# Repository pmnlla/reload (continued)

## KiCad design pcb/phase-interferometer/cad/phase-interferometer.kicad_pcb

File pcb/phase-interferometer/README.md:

# Phase Interferometer
### Max Kendall

At a high level, this is a system that uses 3 antennas (elements) to esitmate the approximate direction of an incoming radio signal. This means that you're able to get the location of an object in a protocol-agnostic manner! The vision is that this is mostly portable (aside from the antennas) and can be whipped out anywhere to get a quick bearing.

The hardware contains 3 RF frontends, including 1 amplifier, 1 mixer, and 1 filter for each element. It uses a mixer to be able to directly feed the signal into the onboard RP2040 microcontroller. It then would perform a phase analysis to determine which signals reach the pins first.
Since we're dealing with a phased-array, we need to perform length tuning to make sure all the tracks are electrically the same length. KiCAD has a great built-in tool for this!

Here's the features/specs:
- RP2040 MCU
- 3x 433 MHz frontends
- USB-C
- 4-layer board
- via fencing/stitching
- broken-out gpio headers for all free pins
- LO for all mixers

## Super cool pics:

Main repository can be found [here](https://github.com/maxsrobotics/phase-interferometer).

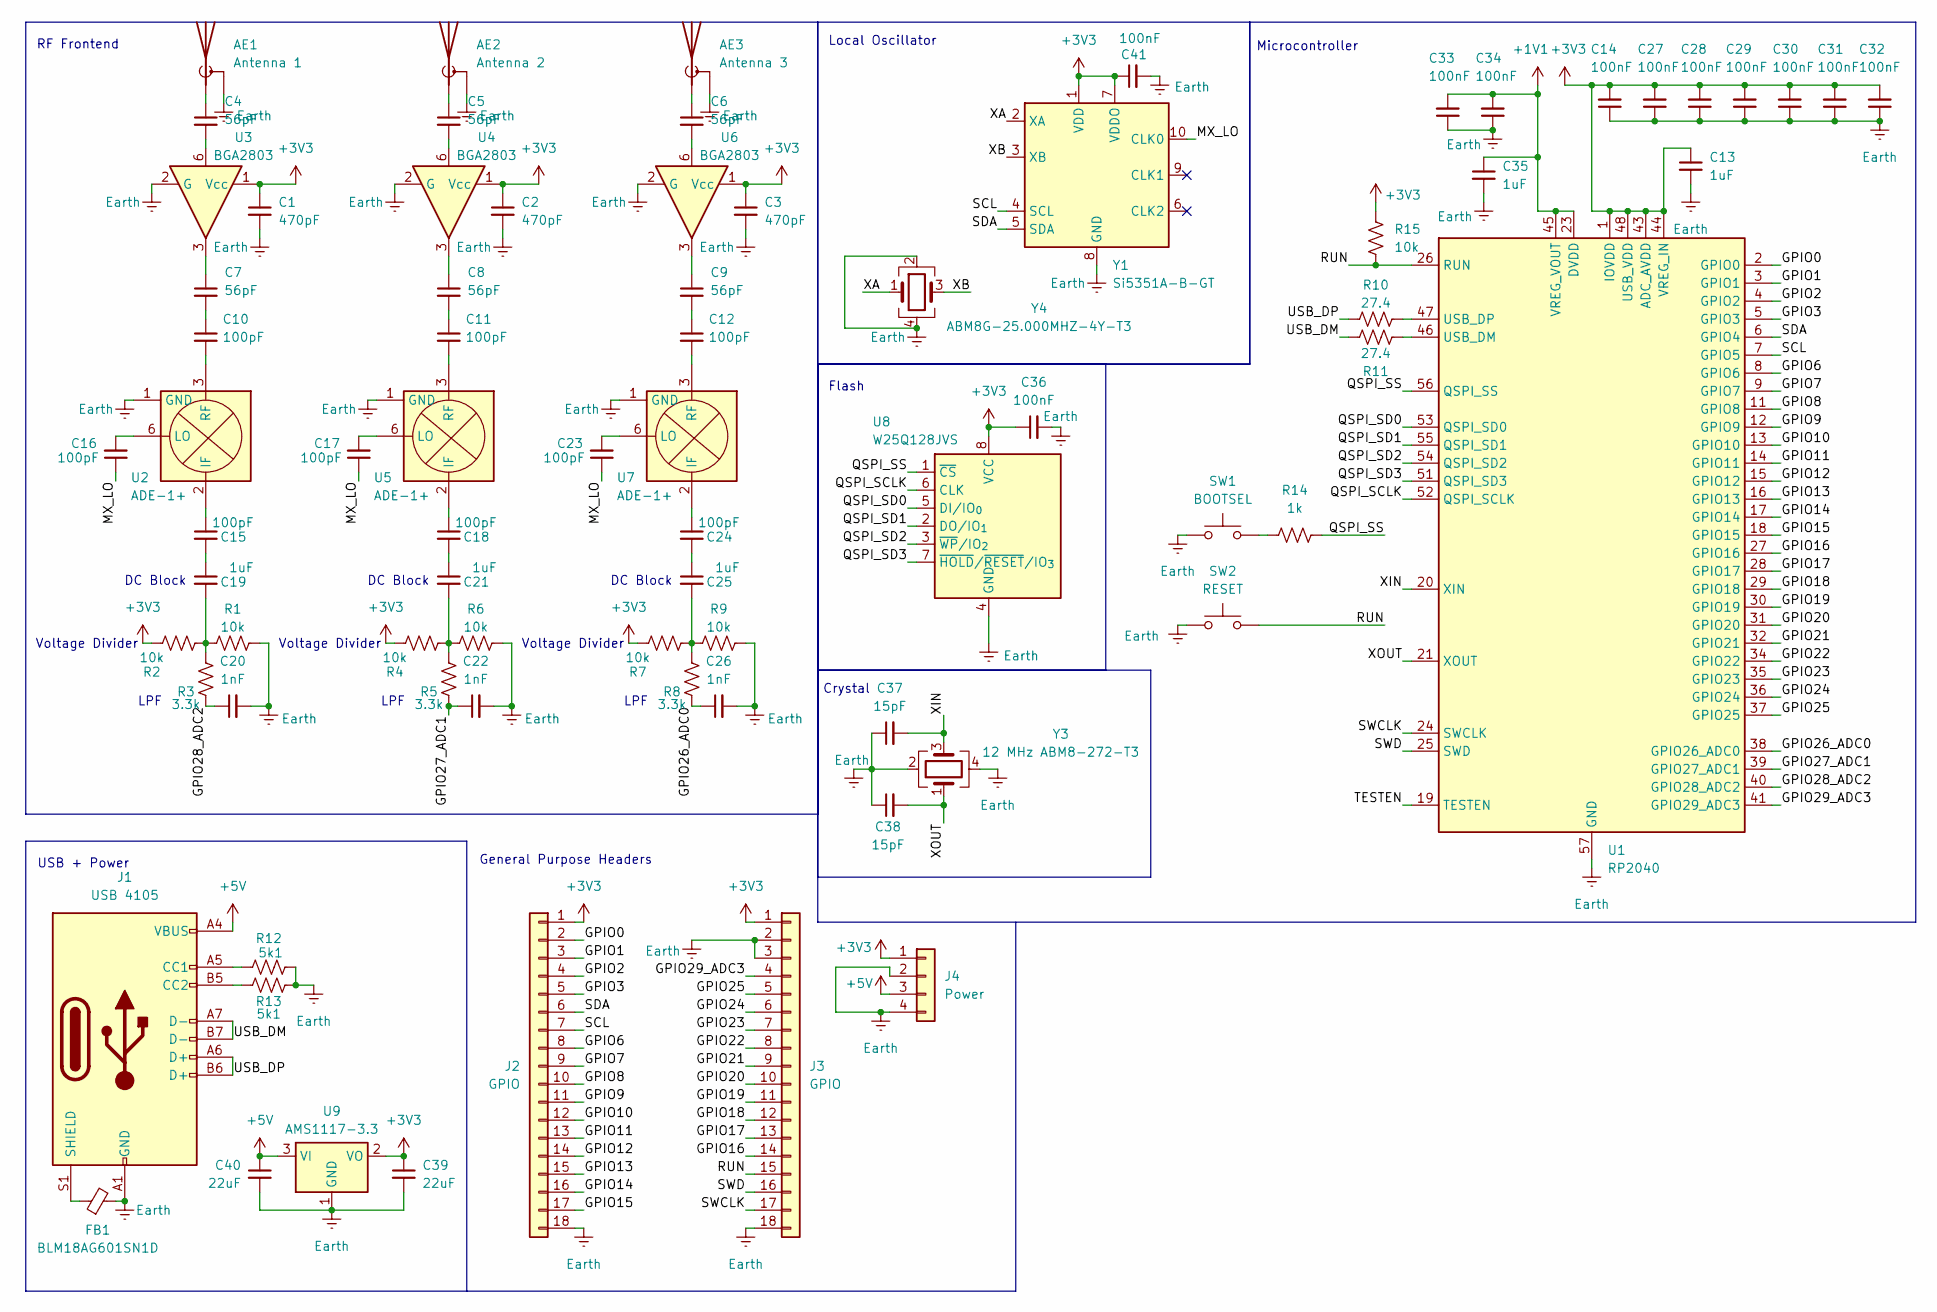
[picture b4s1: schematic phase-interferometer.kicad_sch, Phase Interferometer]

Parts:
AE1: Antenna 1; PinSocket_1x02_P2.54mm_Vertical
AE2: Antenna 2; PinSocket_1x02_P2.54mm_Vertical
AE3: Antenna 3; PinSocket_1x02_P2.54mm_Vertical
C1, C2, C3: 470pF; C_0603_1608Metric
C4, C5, C6, C7, C8, C9: 56pF; C_0603_1608Metric
C10, C11, C12, C15, C16, C17, C18, C23, C24: 100pF; C_0603_1608Metric
C13, C19, C21, C25, C35: 1uF; C_0603_1608Metric
C14, C27, C28, C29, C30, C31, C32, C33, C34, C36, C41: 100nF; C_0603_1608Metric
C20, C22, C26: 1nF; C_0603_1608Metric
C37, C38: 15pF; C_0603_1608Metric
C39, C40: 22uF; C_0603_1608Metric
FB1: BLM18AG601SN1D; R_0201_0603Metric
J1: USB 4105; USB_C_Receptacle_GCT_USB4105-xx-A_16P_TopMnt_Horizontal
J2, J3: GPIO; PinSocket_1x18_P2.54mm_Vertical
J4: Power; PinSocket_1x04_P2.54mm_Vertical
R1, R2, R4, R6, R7, R9, R15: 10k; R_0603_1608Metric
R3, R5, R8: 3.3k; R_0603_1608Metric
R10, R11: 27.4; R_0603_1608Metric
R12, R13: 5k1; R_0603_1608Metric
R14: 1k; R_0603_1608Metric
SW1: BOOTSEL; SW_Tactile_SPST_NO_Straight_CK_PTS636Sx25SMTRLFS
SW2: RESET; SW_Tactile_SPST_NO_Straight_CK_PTS636Sx25SMTRLFS
U1: RP2040; QFN-56-1EP_7x7mm_P0.4mm_EP3.2x3.2mm
U2, U5, U7: ADE-1+; Mini-Circuits_CD636_H4.11mm
U3, U4, U6: BGA2803; SOT-363_SC-70-6
U8: W25Q128JVS; SOIC-8_5.3x5.3mm_P1.27mm
U9: AMS1117-3.3; SOT-223-3_TabPin2
Y1: Si5351A-B-GT; MSOP-10_3x3mm_P0.5mm
Y3: 12 MHz ABM8-272-T3; Crystal_SMD_Abracon_ABM8G-4Pin_3.2x2.5mm
Y4: ABM8G-25.000MHZ-4Y-T3; Crystal_SMD_Abracon_ABM8G-4Pin_3.2x2.5mm

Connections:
+1V1: C33.2, C34.2, C35.1, U1.23 (DVDD), U1.45 (VREG_VOUT), U1.50 (DVDD)
+3V3: C1.1, C2.1, C3.1, C13.1, C14.2, C27.2, C28.2, C29.2, C30.2, C31.2, C32.2, C36.1, C39.1, C41.1, J2.1, J3.1, J4.1, R2.2, R4.2, R7.2, R15.1, U1.1 (IOVDD), U1.10 (IOVDD), U1.22 (IOVDD), U1.33 (IOVDD), U1.42 (IOVDD), U1.43 (ADC_AVDD), U1.44 (VREG_IN), U1.48 (USB_VDD), U1.49 (IOVDD), U3.1 (Vcc), U4.1 (Vcc), U6.1 (Vcc), U8.8 (VCC), U9.2 (VO), Y1.1 (VDD), Y1.7 (VDDO)
+5V: C40.1, J1.A4 (VBUS), J1.A9 (VBUS), J1.B4 (VBUS), J1.B9 (VBUS), J4.3, U9.3 (VI)
/GPIO0: J2.2, U1.2 (GPIO0)
/GPIO1: J2.3, U1.3 (GPIO1)
/GPIO2: J2.4, U1.4 (GPIO2)
/GPIO3: J2.5, U1.5 (GPIO3)
/GPIO6: J2.8, U1.8 (GPIO6)
/GPIO7: J2.9, U1.9 (GPIO7)
/GPIO8: J2.10, U1.11 (GPIO8)
/GPIO9: J2.11, U1.12 (GPIO9)
/GPIO10: J2.12, U1.13 (GPIO10)
/GPIO11: J2.13, U1.14 (GPIO11)
/GPIO12: J2.14, U1.15 (GPIO12)
/GPIO13: J2.15, U1.16 (GPIO13)
/GPIO14: J2.16, U1.17 (GPIO14)
/GPIO15: J2.17, U1.18 (GPIO15)
/GPIO16: J3.14, U1.27 (GPIO16)
/GPIO17: J3.13, U1.28 (GPIO17)
/GPIO18: J3.12, U1.29 (GPIO18)
/GPIO19: J3.11, U1.30 (GPIO19)
/GPIO20: J3.10, U1.31 (GPIO20)
/GPIO21: J3.9, U1.32 (GPIO21)
/GPIO22: J3.8, U1.34 (GPIO22)
/GPIO23: J3.7, U1.35 (GPIO23)
/GPIO24: J3.6, U1.36 (GPIO24)
/GPIO25: J3.5, U1.37 (GPIO25)
/GPIO26_ADC0: C26.1, R8.1, U1.38 (GPIO26_ADC0)
/GPIO27_ADC1: C22.1, R5.1, U1.39 (GPIO27_ADC1)
/GPIO28_ADC2: C20.1, R3.1, U1.40 (GPIO28_ADC2)
/GPIO29_ADC3: J3.4, U1.41 (GPIO29_ADC3)
/MX_LO: C16.1, C17.1, C23.1, Y1.10 (CLK0)
/QSPI_SCLK: U1.52 (QSPI_SCLK), U8.6 (CLK)
/QSPI_SD0: U1.53 (QSPI_SD0), U8.5 (DI/IO_{0})
/QSPI_SD1: U1.55 (QSPI_SD1), U8.2 (DO/IO_{1})
/QSPI_SD2: U1.54 (QSPI_SD2), U8.3 (~WP/IO_{2})
/QSPI_SD3: U1.51 (QSPI_SD3), U8.7 (~HOLD/~RESET/IO_{3})
/QSPI_SS: R14.2, U1.56 (QSPI_SS), U8.1 (~CS)
/RUN: J3.15, R15.2, SW2.2, U1.26 (RUN)
/SCL: J2.7, U1.7 (GPIO5), Y1.4 (SCL)
/SDA: J2.6, U1.6 (GPIO4), Y1.5 (SDA)
/SWCLK: J3.17, U1.24 (SWCLK)
/SWD: J3.16, U1.25 (SWD)
/TESTEN: U1.19 (TESTEN)
/USB_DM: J1.A7 (D-), J1.B7 (D-), R11.2
/USB_DP: J1.A6 (D+), J1.B6 (D+), R10.1
/XA: Y1.2 (XA), Y4.1
/XB: Y1.3 (XB), Y4.3
/XIN: C37.2, U1.20 (XIN), Y3.3
/XOUT: C38.2, U1.21 (XOUT), Y3.1
Earth: AE1.2 (Shield), AE2.2 (Shield), AE3.2 (Shield), C1.2, C2.2, C3.2, C13.2, C14.1, C20.2, C22.2, C26.2, C27.1, C28.1, C29.1, C30.1, C31.1, C32.1, C33.1, C34.1, C35.2, C36.2, C37.1, C38.1, C39.2, C40.2, C41.2, FB1.2, J1.A1 (GND), J1.A12 (GND), J1.B1 (GND), J1.B12 (GND), J2.18, J3.2, J3.3, J3.18, J4.2, J4.4, R1.2, R6.2, R9.2, R12.2, R13.2, SW1.1, SW2.1, U1.57 (GND), U2.1 (GND), U2.4 (GND), U2.5 (GND), U3.2 (G), U3.4 (G), U3.5 (G), U4.2 (G), U4.4 (G), U4.5 (G), U5.1 (GND), U5.4 (GND), U5.5 (GND), U6.2 (G), U6.4 (G), U6.5 (G), U7.1 (GND), U7.4 (GND), U7.5 (GND), U8.4 (GND), U9.1 (GND), Y1.8 (GND), Y3.2, Y3.4, Y4.2, Y4.4
unnamed: AE1.1 (A), C4.1
unnamed: AE2.1 (A), C5.1
unnamed: AE3.1 (A), C6.1
unnamed: C4.2, U3.6
unnamed: C5.2, U4.6
unnamed: C6.2, U6.6
unnamed: C7.1, U3.3
unnamed: C8.1, U4.3
unnamed: C9.1, U6.3
unnamed: C7.2, C10.1
unnamed: C8.2, C11.1
unnamed: C9.2, C12.1
unnamed: C15.2, C19.1
unnamed: C18.2, C21.1
unnamed: C19.2, R1.1, R2.1, R3.2
unnamed: C21.2, R4.1, R5.2, R6.1
unnamed: C24.2, C25.1
unnamed: C25.2, R7.1, R8.2, R9.1
unnamed: J1.A5 (CC1), R12.1
unnamed: J1.B5 (CC2), R13.1
unnamed: FB1.1, J1.S1 (SHIELD)
unnamed: R14.1, SW1.2
unnamed: R11.1, U1.46 (USB_DM)
unnamed: R10.2, U1.47 (USB_DP)
unnamed: C15.1, U2.2 (IF)
unnamed: C16.2, U2.6 (LO)
unnamed: C10.2, U2.3 (RF)
unnamed: C18.1, U5.2 (IF)
unnamed: C17.2, U5.6 (LO)
unnamed: C11.2, U5.3 (RF)
unnamed: C24.1, U7.2 (IF)
unnamed: C23.2, U7.6 (LO)
unnamed: C12.2, U7.3 (RF)

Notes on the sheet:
LPF
Local Oscillator
Voltage Divider
DC Block
USB + Power
General Purpose Headers
Microcontroller
Flash
Crystal
RF Frontend

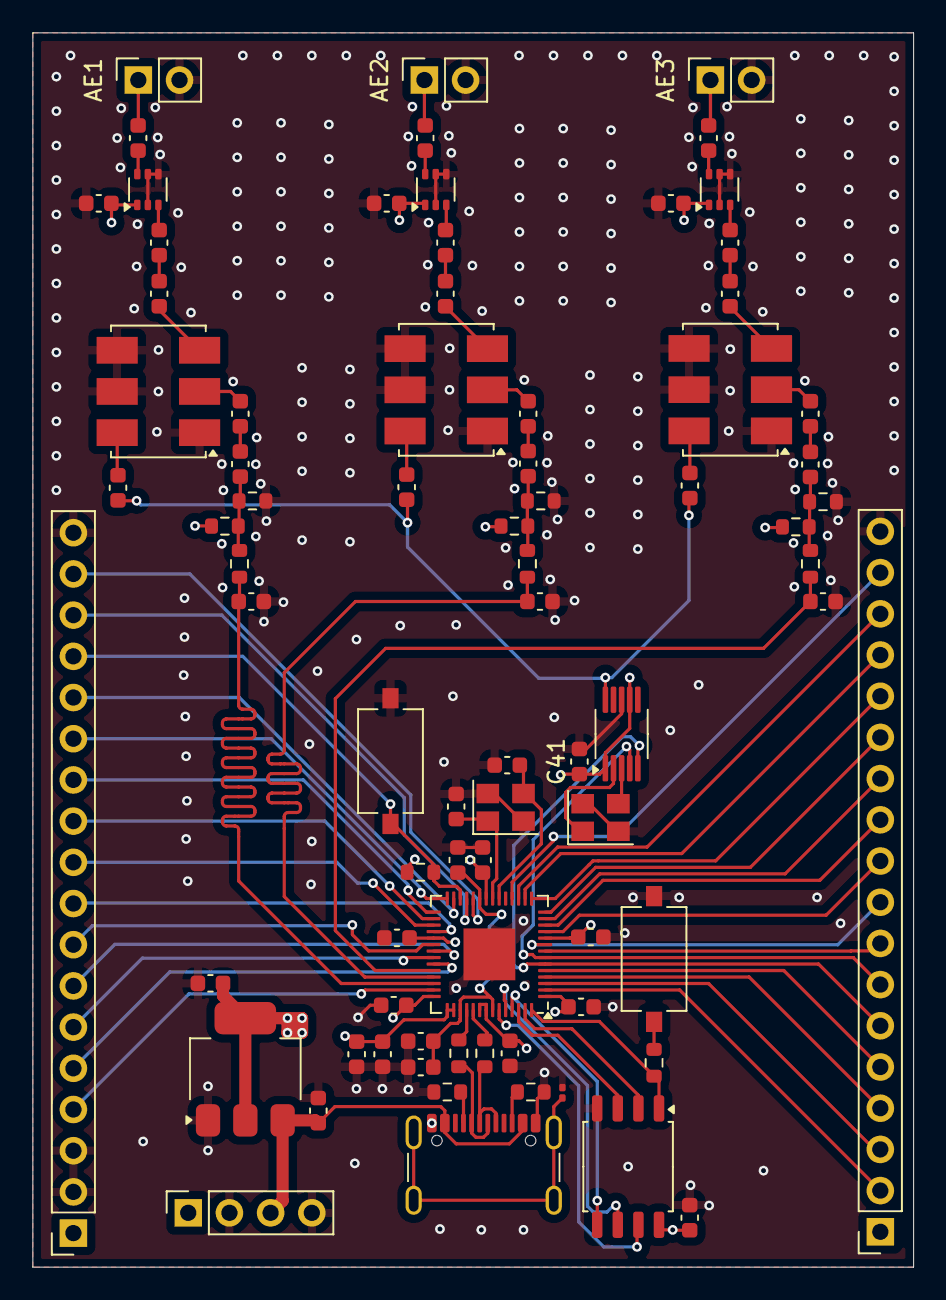
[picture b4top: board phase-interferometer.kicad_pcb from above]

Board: 4 copper layers, 54.3 x 76.1 mm, 78 parts (0 on the bottom side), 83 nets.

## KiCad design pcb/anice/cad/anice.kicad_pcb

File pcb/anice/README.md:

# Anice

*"FPGAs work like this. You don't tell them what to do, you tell them what to BE."*

An FPGA is a chip that can be configured on the hardware level. You can basically make your own CPU and GPU on it.

The PCB called is "anice":
- 256MiB of ram
- 128MiB of flash
- HDMI port
- triple USB C with JTAG converter
- SDCard Reader
- dual 25MHz clock and 200MHz built-in clock
- multiple indicator lights
- only 4 layer PCB

View online demo on [kicanvas](https://kicanvas.org/?github=https%3A%2F%2Fgithub.com%2Fcheyao%2Fanice%2Ftree%2Fmain%2Fsrc%2F)!

## Anice:

This was the alpha version of my newer [Icepi Zero](https://github.com/cheyao/icepi-zero)!

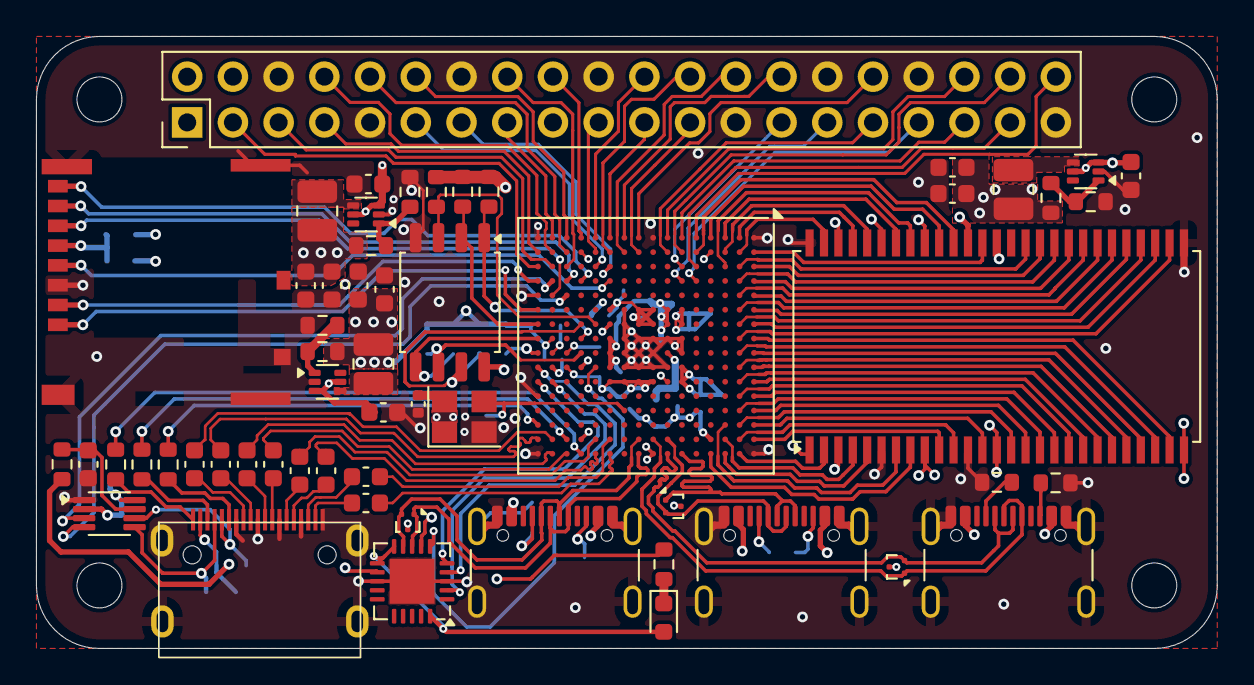
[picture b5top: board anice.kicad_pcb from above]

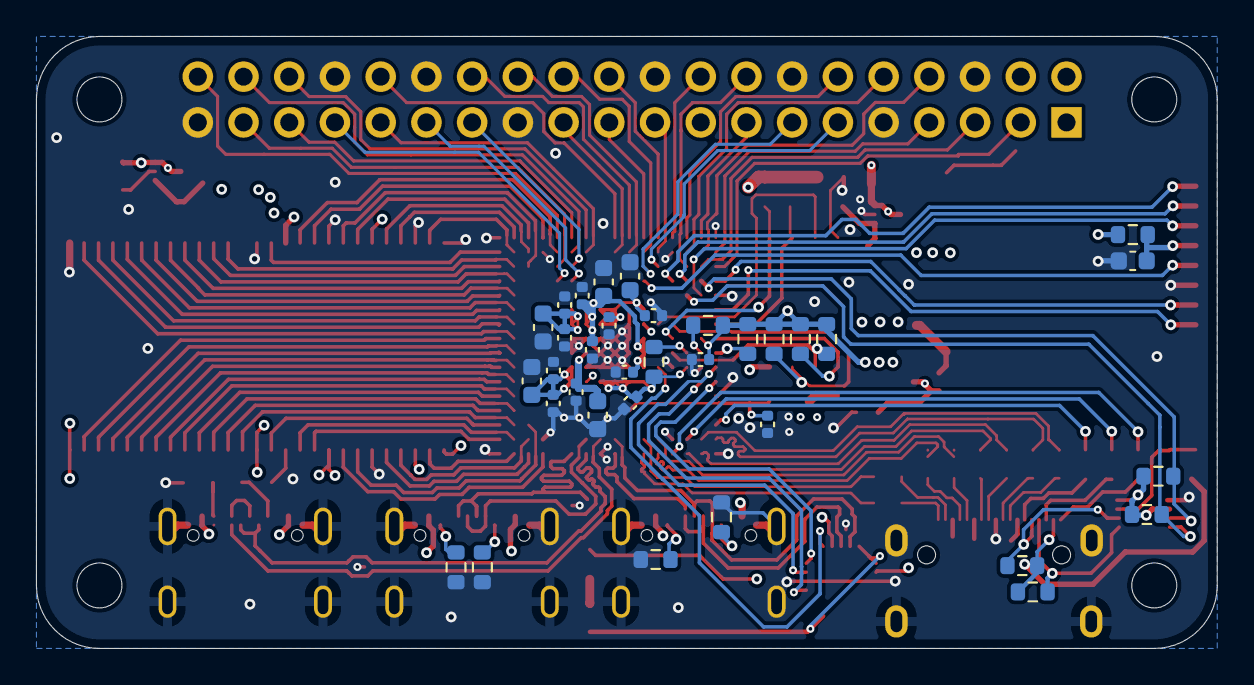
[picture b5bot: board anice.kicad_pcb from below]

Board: 4 copper layers, 65.6 x 34.0 mm, 95 parts (34 on the bottom side), 141 nets.

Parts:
C2, C3, C4, C8, C9, C11, C12, C25, C28, C30, C32: 10uF; C_0603_1608Metric
C10, C21, C27, C29: 100pF; C_0603_1608Metric
C13, C14, C15, C16, C17, C18, C19, C20: 22nF; C_0603_1608Metric
C22: 22uF; C_0603_1608Metric
C23, C26, C31, C33, C34, C35, C36, C37, C38, C39, C41, C42, C43: 100nF; C_0402_1005Metric
C40: 15pF; C_0402_1005Metric
D1: RED; LED_0603_1608Metric
H1, H2, H3, H4: MountingHole_Pad; MountingHole_2.5mm
J1: Conn_02x20_Counter_Clockwise; PinHeader_2x20_P2.54mm_Vertical
J2: Micro_SD_Card_Det1; SDCard molex
J3, J4, J5: USB_C_Receptacle_USB2.0_14P; USB_C_Receptacle_GCT_USB4105-xx-A_16P_TopMnt_Horizontal
J7: HDMI_C_1.3; XKB Connection A71-05H4-111N1
L1, L2, L3: 2.2uH; L_1008_2520Metric
R1, R2, R3, R4, R6, R7: 5.1k; R_0603_1608Metric
R5: 549; R_0603_1608Metric
R8, R10: 470; R_0603_1608Metric
R9, R19, R20, R21, R22: 10k; R_0603_1608Metric
R11: 100k; R_0603_1608Metric
R12, R13, R16, R17, R23, R24: 4.7k; R_0603_1608Metric
R14, R15: 3.3k; R_0603_1608Metric
R18: 1k; R_0603_1608Metric
R38: 0.47; R_0603_1608Metric
RA1, RA2, RA3: 15k; R_0603_1608Metric
RB1: 18k; R_0603_1608Metric
RB2: 4.7k; R_0603_1608Metric
RB3: 3.3k; R_0603_1608Metric
U1: ECP5U_12_CABGA256; BGA-256_14.0x14.0mm_Layout16x16_P0.8mm_Ball0.45mm_Pad0.32mm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
U5, U6, U8: TPD2EUSB30; Texas_DRT-3
U7: FT231XQ; QFN-20-1EP_4x4mm_P0.5mm_EP2.5x2.5mm
U9: PCA9306DC1; VSSOP-8_2.3x2mm_P0.5mm
U10: W9825G6KH-6; TSOP-II-54_22.2x10.16mm_P0.8mm
U11: W25Q128JVS; SOIC-8_5.3x5.3mm_P1.27mm
U12, U13, U14: TLV62569DRL; SOT-563
Y1: ECS-2520MV-xxx-xx; Crystal_SMD_3225-4Pin_3.2x2.5mm

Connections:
+1V1: C2.1, C3.1, C28.1, C29.1, C36.1, C37.1, C38.1, C42.1, L1.2, RA1.1, U1.G6 (VCC[6]), U1.G7 (VCC[6]), U1.G9 (VCC[6]), U1.L8 (VCC[6]), U1.L9 (VCC[6]), U1.L10 (VCC[6])
+2V5: C11.1, C27.1, L2.2, RA2.1, U1.G11 (VCCAUX[2]), U1.L7 (VCCAUX[2])
+3V3: C9.1, C10.1, C23.2, C25.2, C26.2, C30.2, C31.2, C32.2, C33.2, C34.2, C35.2, C39.1, C41.2, C43.1, J1.1, J1.17, L3.2, R14.1, R15.1, R16.1, R17.1, R18.1, R19.1, R20.1, R21.1, R22.1, R23.1, R24.1, R38.2, RA3.1, U1.F6 (VCCIO0[2]), U1.F7 (VCCIO0[2]), U1.F10 (VCCIO1[2]), U1.F11 (VCCIO1[2]), U1.H6 (VCCIO7[2]), U1.H7 (VCCIO7[2]), U1.H11 (VCCIO2[2]), U1.J6 (VCCIO6[2]), U1.J7 (VCCIO6[2]), U1.J11 (VCCIO2[2]), U1.K11 (VCCIO3[2]), U1.L6 (VCCIO8), U1.L11 (VCCIO3[2]), U1.P10 (CFG_1), U1.R8 (PB13A/+/SN/CSN), U9.2 (VREF1), U9.8 (EN), U10.1 (VDD), U10.3 (VDDQ), U10.9 (VDDQ), U10.14 (VDD), U10.27 (VDD), U10.43 (VDDQ), U10.49 (VDDQ), U11.8 (VCC), Y1.1 (Tri-State), Y1.4 (VDD)
+5V: C4.1, C8.1, C12.1, J1.2, J1.4, J3.A4 (VBUS), J3.A9 (VBUS), J3.B4 (VBUS), J3.B9 (VBUS), J4.A4 (VBUS), J4.A9 (VBUS), J4.B4 (VBUS), J4.B9 (VBUS), J5.A4 (VBUS), J5.A9 (VBUS), J5.B4 (VBUS), J5.B9 (VBUS), J7.18 (+5V), R11.1, R12.1, R13.1, U7.12 (VCC), U12.3 (VIN), U12.5 (EN), U13.3 (VIN), U13.5 (EN), U14.3 (VIN), U14.5 (EN)
/Power/FB1: RA1.2, RB1.2, U14.1 (FB)
/Power/FB2: RA2.2, RB2.2, U13.1 (FB)
/Power/FB3: RA3.2, RB3.2, U12.1 (FB)
/Power/L1: L1.1, U14.4 (SW)
/Power/L2: L2.1, U13.4 (SW)
/Power/L3: L3.1, U12.4 (SW)
/USB/LED_TXLED: D1.1 (K), R5.2
CLK: R18.2, U1.N9 (CCLK/MCLK/SCK), U11.6 (CLK)
CONN3: J1.3, U1.T3 (PL41D/-/LDQ44)
CONN5: J1.5, U1.R3 (PL41B/-/HS/LDQ44)
CONN7: J1.7, U1.T2 (PL38D/-/LDQ44)
CONN8: J1.8, U1.R2 (PL38C/+/LDQ44)
CONN10: J1.10, U1.P2 (PL32B/-/HS/LDQSN32)
CONN11: J1.11, U1.M3 (PL32D/-/LDQ32)
CONN12: J1.12, U1.P1 (PL35A/+/HS/LDQ32)
CONN13: J1.13, U1.L3 (PL32C/+/LDQ32)
CONN15: J1.15, U1.R1 (PL35B/-/VREF1_6/HS/LDQ32)
CONN16: J1.16, U1.P3 (PL38B/-/HS/LDQ44)
CONN18: J1.18, U1.N1 (PL32A/+/HS/LDQS32)
CONN19: J1.19, U1.M2 (PL26D/-/PCLKC6_0/LDQ32)
CONN21: J1.21, U1.L1 (PL26A/+/PCLKT6_1/HS/LDQ32)
CONN22: J1.22, U1.M1 (PL26C/+/PCLKT6_0/LDQ32)
CONN23: J1.23, U1.J2 (PL23B/-/PCLKC7_1/HS/LDQ20)
CONN24: J1.24, U1.L2 (PL26B/-/PCLKC6_1/HS/LDQ32)
CONN26: J1.26, U1.K2 (PL23D/-/PCLKC7_0/LDQ20)
CONN27: J1.27, U1.F3 (PL5D/-/LDQ8)
CONN28: J1.28, U1.K1 (PL23C/+/PCLKT7_0/LDQ20)
CONN29: J1.29, U1.F4 (PL8C/+/LDQ8)
CONN31: J1.31, U1.G2 (PL14B/-/HS/LDQ20)
CONN32: J1.32, U1.J1 (PL23A/+/PCLKT7_1/HS/LDQ20)
CONN33: J1.33, U1.E4 (PT9A/+)
CONN35: J1.35, U1.F1 (PL14A/+/HS/LDQ20)
CONN36: J1.36, U1.G1 (PL20A/+/GR_PCLK7_1/HS/LDQS20)
CONN37: J1.37, U1.E3 (PL5C/+/LDQ8)
CONN38: J1.38, U1.F2 (PL11C/+/LDQ8)
CONN40: J1.40, U1.E1 (PL11D/-/LDQ8)
D1+: J3.A6 (D+), J3.B6 (D+), U1.J16 (PR23A/+/PCLKT2_1/HS/RDQ20), U7.8 (USBDP), U8.1 (D+)
D1-: J3.A7 (D-), J3.B7 (D-), U1.J15 (PR23B/-/PCLKC2_1/HS/RDQ20), U7.9 (USBDM), U8.2 (D-)
D2+: J4.A6 (D+), J4.B6 (D+), U1.F16 (PR14A/+/HS/RDQ20), U6.1 (D+)
D2-: J4.A7 (D-), J4.B7 (D-), U1.G15 (PR14B/-/HS/RDQ20), U6.2 (D-)
D3+: J5.A6 (D+), J5.B6 (D+), U1.H15 (PR20B/-/HS/RDQSN20), U5.1 (D+)
D3-: J5.A7 (D-), J5.B7 (D-), U1.G16 (PR20A/+/GR_PCLK2_1/HS/RDQS20), U5.2 (D-)
DONE: R17.2, U1.P9 (DONE)
FPDI_CEC: R8.2, U1.T14 (PR41D/-/RDQ44)
FPDI_CLK+: C19.1, U1.T15 (PR38D/-/RDQ44)
FPDI_CLK-: C20.1, U1.R15 (PR38C/+/RDQ44)
FPDI_D0+: C17.1, U1.P16 (PR35A/+/HS/RDQ32)
FPDI_D0-: C18.1, U1.R16 (PR35B/-/VREF1_3/HS/RDQ32)
FPDI_D1+: C15.1, U1.M16 (PR26C/+/PCLKT3_0/RDQ32)
FPDI_D1-: C16.1, U1.M15 (PR26D/-/PCLKC3_0/RDQ32)
FPDI_D2+: C13.1, U1.L16 (PR26A/+/PCLKT3_1/HS/RDQ32)
FPDI_D2-: C14.1, U1.L15 (PR26B/-/PCLKC3_1/HS/RDQ32)
FPDI_HPD: R10.2, U1.N16 (PR32A/+/HS/RDQS32)
FPDI_SCL: R15.2, U1.R4 (PL41C/+/LDQ44), U9.3 (SCL1)
FPDI_SDA: R14.2, U1.P5 (PL47D/-/LLC_GPLL0C_IN/LDQ44), U9.4 (SDA1)
FPDI_UTIL: R9.2, U1.P15 (PR32B/-/HS/RDQSN32)
FT2V5: D1.2 (A), U7.10 (3V3OUT), U7.11 (~RESET), U7.20 (VCCIO)
FTDI_nTXLED: R5.1, U7.7 (CBUS2)
GCLK: C40.1, U1.K13 (PR29A/+/GR_PCLK3_0/HS/RDQ32), Y1.3 (OUT)
GND: C2.2, C3.2, C4.2, C8.2, C9.2, C10.2, C11.2, C12.2, C21.2, C22.2, C23.1, C25.1, C26.1, C27.2, C28.2, C29.2, C30.1, C31.1, C32.1, C33.1, C34.1, C35.1, C36.2, C37.2, C38.2, C39.2, C40.2, C41.1, C42.2, C43.2, J1.6, J1.9, J1.14, J1.20, J1.25, J1.30, J1.34, J1.39, J2.6 (VSS), J2.9 (DET_B), J2.11 (SHIELD), J3.A1 (GND), J3.A12 (GND), J3.B1 (GND), J3.B12 (GND), J3.S1 (SHIELD), J4.A1 (GND), J4.A12 (GND), J4.B1 (GND), J4.B12 (GND), J4.S1 (SHIELD), J5.A1 (GND), J5.A12 (GND), J5.B1 (GND), J5.B12 (GND), J5.S1 (SHIELD), J7.1 (D2S), J7.4 (D1S), J7.7 (D0S), J7.10 (CKS), J7.13 (GND), J7.SH, R1.1, R2.1, R3.1, R4.1, R6.1, R7.1, RB1.1, RB2.1, RB3.1, U1.A1 (GND[27]), U1.A16 (GND[27]), U1.D2 (GND[27]), U1.D15 (GND[27]), U1.F8 (GND[27]), U1.F9 (GND[27]), U1.G8 (GND[27]), U1.G10 (GND[27]), U1.H1 (GND[27]), U1.H8 (GND[27]), U1.H9 (GND[27]), U1.H10 (GND[27]), U1.H16 (GND[27]), U1.J8 (GND[27]), U1.J9 (GND[27]), U1.J10 (GND[27]), U1.K6 (GND[27]), U1.K7 (GND[27]), U1.K8 (GND[27]), U1.K9 (GND[27]), U1.K10 (GND[27]), U1.N2 (GND[27]), U1.N10 (CFG_0), U1.N15 (GND[27]), U1.R10 (CFG_2), U1.T1 (GND[27]), U1.T5 (GND[27]), U1.T12 (GND[27]), U1.T16 (GND[27]), U5.3 (GND), U6.3 (GND), U7.3 (GND), U7.13 (GND), U7.21 (GND), U8.3 (GND), U9.1 (GND), U10.6 (VSSQ), U10.12 (VSSQ), U10.28 (VSS), U10.41 (VSS), U10.46 (VSSQ), U10.52 (VSSQ), U10.54 (VSS), U11.4 (GND), U12.2 (GND), U13.2 (GND), U14.2 (GND), Y1.2 (GND)
GPDI_SCL: J7.15 (SCL), R12.2, U9.6 (SCL2)
GPDI_SDA: J7.16 (SDA), R13.2, U9.5 (SDA2)
INITN: R16.2, U1.T9 (INITN)
IO0: R22.2, U1.T8 (PB11B/-/D0/MOSI/IO0), U11.5 (DI/IO_{0})
IO1: R21.2, U1.T7 (PB11A/+/D1/MISO/IO1), U11.2 (DO/IO_{1})
IO2: R20.2, U1.M7 (PB9B/-/D2/IO2), U11.3 (~WP/IO_{2})
IO3: R19.2, U1.N7 (PB9A/+/D3/IO3), U11.7 (~HOLD/~RESET/IO_{3})
JTAG_TCK: U1.T10 (TCK), U7.4 (~DSR)
JTAG_TDI: U1.R11 (TDI), U7.2 (~RI)
JTAG_TDO: U1.M10 (TDO), U7.6 (~CTS)
JTAG_TMS: U1.T11 (TMS), U7.5 (~DCD)
unnamed: C22.1, J2.4 (VDD), R38.1
unnamed: J3.A5 (CC1), R1.2
unnamed: J3.B5 (CC2), R2.2
unnamed: J4.A5 (CC1), R3.2
unnamed: J4.B5 (CC2), R4.2
unnamed: J5.A5 (CC1), R6.2
unnamed: J5.B5 (CC2), R7.2
unnamed: J7.14 (CEC), R8.1
unnamed: C19.2, J7.11 (CK+)
unnamed: C20.2, J7.12 (CK-)
unnamed: C17.2, J7.8 (D0+)
unnamed: C18.2, J7.9 (D0-)
unnamed: C15.2, J7.5 (D1+)
unnamed: C16.2, J7.6 (D1-)
unnamed: C13.2, J7.2 (D2+)
unnamed: C14.2, J7.3 (D2-)
unnamed: J7.19 (HPD), R10.1
unnamed: J7.17 (UTILITY), R9.1
unnamed: R23.2, U1.R9 (PROGRAMN)
unnamed: C21.1, R11.2, U9.7 (VREF2)
SDRAM_A0: U1.B10 (PT44A/+), U10.23 (A0)
SDRAM_A1: U1.A9 (PT42A/+), U10.24 (A1)
SDRAM_A2: U1.B9 (PT38A/+/GR_PCLK1_0), U10.25 (A2)
SDRAM_A3: U1.A8 (PT29B/-/PCLKC0_0), U10.26 (A3)
SDRAM_A4: U1.B8 (PT35B/-/PCLKC1_0), U10.29 (A4)
SDRAM_A5: U1.A7 (PT29A/+/PCLKT0_0), U10.30 (A5)
SDRAM_A6: U1.B7 (PT27B/-/PCLKC0_1), U10.31 (A6)
SDRAM_A7: U1.A6 (PT18B/-), U10.32 (A7)
SDRAM_A8: U1.B6 (PT22B/-), U10.33 (A8)
SDRAM_A9: U1.A5 (PT18A/+), U10.34 (A9)
SDRAM_A10: U1.A10 (PT42B/-), U10.22 (A10/AP)
SDRAM_A11: U1.B5 (PT15B/-), U10.35 (A11)
SDRAM_A12: U1.A4 (PT6B/-), U10.36 (A12)
SDRAM_BA0: U1.A11 (PT53A/+), U10.20 (BS0)
SDRAM_BA1: U1.B11 (PT49A/+), U10.21 (BS1)
SDRAM_CKE: U1.B4 (PT11B/-), U10.37 (CKE)
SDRAM_CLK: U1.A3 (PT6A/+), U10.38 (CLK)
SDRAM_D0: U1.B16 (PR2A/+/HS/RDQ8), U10.2 (DQ0)
SDRAM_D1: U1.C15 (PR5B/-/HS/RDQ8), U10.4 (DQ1)
SDRAM_D2: U1.C16 (PR5A/+/HS/RDQ8), U10.5 (DQ2)
SDRAM_D3: U1.C14 (PR2C/+/RDQ8), U10.7 (DQ3)
SDRAM_D4: U1.D16 (PR8A/+/HS/RDQS8), U10.8 (DQ4)
SDRAM_D5: U1.A15 (PT67B/-), U10.10 (DQ5)
SDRAM_D6: U1.B15 (PR2B/-/S0_IN/HS/RDQ8), U10.11 (DQ6)
SDRAM_D7: U1.A14 (PT65B/-), U10.13 (DQ7)
SDRAM_D8: U1.A2 (PT4A/+), U10.42 (DQ8)
SDRAM_D9: U1.E2 (PL8B/-/HS/LDQSN8), U10.44 (DQ9)
SDRAM_D10: U1.D1 (PL8A/+/HS/LDQS8), U10.45 (DQ10)
SDRAM_D11: U1.C3 (PL2C/+/LDQ8), U10.47 (DQ11)
SDRAM_D12: U1.C1 (PL5A/+/HS/LDQ8), U10.48 (DQ12)
SDRAM_D13: U1.C2 (PL5B/-/HS/LDQ8), U10.50 (DQ13)
SDRAM_D14: U1.B1 (PL2A/+/HS/LDQ8), U10.51 (DQ14)
SDRAM_D15: U1.B2 (PL2B/-/HS/LDQ8), U10.53 (DQ15)
SDRAM_DQM0: U1.B14 (PT67A/+), U10.15 (LDQM)
SDRAM_DQM1: U1.B3 (PT4B/-), U10.39 (UDQM)
SDRAM_nCAS: U1.B13 (PT60A/+), U10.17 (~CAS)
SDRAM_nCS: U1.B12 (PT56A/+), U10.19 (~CS)
SDRAM_nRAS: U1.A12 (PT53B/-), U10.18 (~RAS)
SDRAM_nWE: U1.A13 (PT65A/+), U10.16 (~WE)
SD_CLK: J2.5 (CLK), U1.L4 (PL29C/+/GR_PCLK6_1/LDQ32)
SD_CMD: J2.3 (CMD), U1.R5 (PL44A/+/HS/LDQS44)
SD_D0: J2.7 (DAT0), U1.T4 (PL44B/-/HS/LDQSN44)
SD_D1: J2.8 (DAT1), U1.T6 (PB4A/+/D7/IO7)
SD_D2: J2.1 (DAT2), U1.N4 (PL38A/+/HS/LDQ44)
SD_D3: J2.2 (DAT3/CD), U1.P4 (PL41A/+/HS/LDQ44)
~CS: R24.2, U1.N8 (PB15A/+/HOLDN/DI/BUSY/CSSPIN/CEN), U11.1 (~CS)

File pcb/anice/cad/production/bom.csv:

Designator,Footprint,Quantity,Value,LCSC Part #
"C10, C27, C29",0603,3,100pF,
"C11, C25, C28, C30, C32, C9",0603,6,10uF,
"C12, C2, C3, C4, C8",0603,5,10uF,
"C13, C14, C15, C16, C17, C18, C19, C20",0603,8,22nF,
C21,0603,1,100pF,
C22,0603,1,22uF,CC0805ZKY5V5BB226 
"C23, C26, C31, C33, C34, C35, C36, C37, C38, C39, C41, C42, C43",0402,13,100nF,
C40,0402,1,15pF,
D1,0603,1,RED,
J1,PinHeader_2x20_P2.54mm_Vertical,1,Conn_02x20_Counter_Clockwise,
J2,SDCard molex,1,Micro_SD_Card_Det1,C20613194
"J3, J4, J5",USB_C_Receptacle_GCT_USB4105-xx-A_16P_TopMnt_Horizontal,3,USB_C_Receptacle_USB2.0_14P, C2765186
J7,XKB Connection A71-05H4-111N1,1,HDMI_C_1.3,C2682170 
"L1, L2, L3",1008,3,2.2uH, C285758
"R1, R2, R3, R4, R6, R7",0603,6,5.1k,
"R10, R8",0603,2,470,
R11,0603,1,100k,
"R12, R13, RB2",0603,3,4.7k,
"R14, R15, RB3",0603,3,3.3k,
"R16, R17, R24",0603,3,4.7k,AC0603FR-104K7L
R18,0603,1,1k,
R19,0603,1,10k,C15401
"R20, R21, R22, R9",0603,4,10k,
R23,0603,1,4.7k,
R38,0603,1,0.47,C158884
R5,0603,1,549,
"RA1, RA2, RA3",0603,3,15k,
RB1,0603,1,18k,
U1,BGA-256_14.0x14.0mm_Layout16x16_P0.8mm_Ball0.45mm_Pad0.32mm_NSMD,1,ECP5U_12_CABGA256, C1521614
U10,TSOP-II-54_22.2x10.16mm_P0.8mm,1,W9825G6KH-6, C62246
U11,SOIC-8_5.3x5.3mm_P1.27mm,1,W25Q128JVS, C97521
"U12, U13, U14",SOT-563,3,TLV62569DRL,C163217
"U5, U6, U8",Texas_DRT-3,3,TPD2EUSB30,
U7,QFN-20-1EP_4x4mm_P0.5mm_EP2.5x2.5mm,1,FT231XQ,
U9,VSSOP-8_2.3x2mm_P0.5mm,1,PCA9306DC1,
Y1,Crystal_SMD_3225-4Pin_3.2x2.5mm,1,ECS-2520MV-xxx-xx, C5189451

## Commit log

2025-05-16 Add anice
2025-05-17 add phase interferometer
2025-05-17 add reflow example pcb - not done
2025-05-17 idk what claude was doing but woop woop
2025-05-17 dont merge yet
2025-05-17 add design rules
2025-05-17 we gotta swap to more smd
2025-05-20 file a radar.
2025-05-22 revision 1 is mostly done, needs silkscreen and edge cuts to be remade
2025-05-23 PCB BADGE
2025-05-23 from gitbash new done ihope
2025-05-23 update:
2025-05-24 add usb charging hub :D
2025-05-24 Create LICENSE
2025-05-25 forgot how vias work
2025-05-26 fix errors :3
2025-05-26 add schematic and images
2025-06-07 Update CI with full python rebuild!
2025-06-07 documentation woop
2025-06-15 Swap over to an odd way to do reflection. Thanks GPT! ........................................ (All code has been audited by me. Nothing happens that I'm unaware of. This pipeline is not built on vib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
2025-06-15 add a haphazardous file ownership checkl
2025-06-15 update docs
2025-06-15 sooo i broke CI.
2025-07-07 idk do some logging things
